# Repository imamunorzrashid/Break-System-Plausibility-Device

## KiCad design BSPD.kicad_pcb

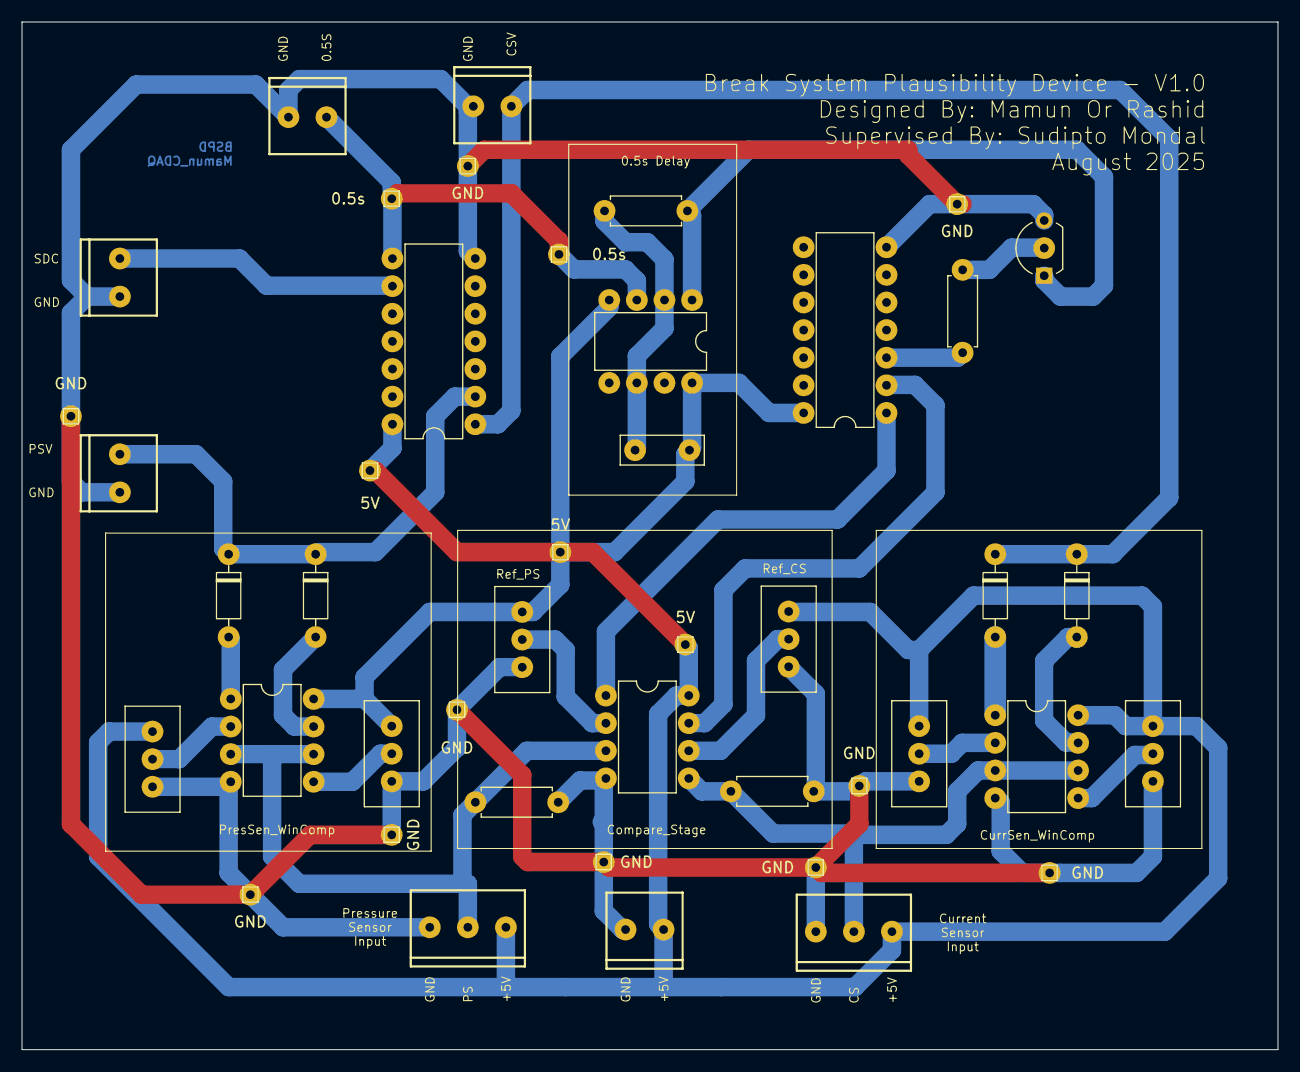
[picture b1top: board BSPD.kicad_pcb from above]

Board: 2 copper layers, 115.5 x 94.5 mm, 44 parts (0 on the bottom side), 24 nets.

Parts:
0.5s, 0.5s#2, 5V, 5V#2, 5V#3: TestPoint_THTPad_1.0x1.0mm_Drill0.5mm
C3: 10uF; C_Disc_D7.5mm_W2.5mm_P5.00mm
D1, D2, D3, D4: D; D_DO-35_SOD27_P7.62mm_Horizontal
GND: TestPoint_THTPad_1.0x1.0mm_Drill0.5mm
GND#2, GND#3, GND#4, GND#5, GND#6, GND#7, GND#8, GND#9, GND#10: TestPoint_THTPad_1.0x1.0mm_Drill0.5mm
J1, J2, J5, J6, J7: Screw_Terminal_3.5mm_2; Screw_Terminal_3.5mm-2
J3, J4: Screw_Terminal_3.5mm_3; Screw_Terminal_3.5mm-3
Q3: NPN; TO-92L_Inline_Wide
R1, R2, R21: 1k; R_Axial_DIN0207_L6.3mm_D2.5mm_P7.62mm_Horizontal
R4: 45.5k; R_Axial_DIN0207_L6.3mm_D2.5mm_P7.62mm_Horizontal
RV1, RV2: 10k; Potentiometer_Bourns_3296W_Vertical
RV3, RV4, RV5, RV6: 1k; Potentiometer_Bourns_3296W_Vertical
U1, U2, U6: LM358; DIP-8_W7.62mm
U3: 4075; DIP-14_W7.62mm
U4: LM555xN; DIP-8_W7.62mm
U7: SN74LS08N; DIP-14_W7.62mm

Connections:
+5V: 5V.1, 5V#2.1, 5V#3.1, C3.2, J3.3, J4.3, J7.2, RV1.1, RV2.1, RV3.1, RV4.1, RV5.1, RV6.1, U1.8 (V+), U2.8 (V+), U3.14 (VDD), U4.4 (R), U4.8 (VCC), U6.8 (V+), U7.14 (VCC)
/0.5s_delay: 0.5s.1, 0.5s#2.1, J5.1, U3.8, U4.3 (Q)
/2: C3.1, R4.2, U4.2 (TR), U4.6 (THR)
/Current_Comp_Out: U6.7, U7.2 (1B)
/Current_Sensor: J3.2, R2.1, U1.3 (+), U1.6 (-), U6.5 (+)
/Current_Sensor_Validated: D1.1 (K), D2.1 (K), J6.1, U3.1
/Pressure_Comp_Out: U6.1, U7.1 (1A)
/Pressure_Sensor: J4.2, R1.1, U2.3 (+), U2.6 (-), U6.3 (+)
/Pressure_Sensor_Validated: D3.1 (K), D4.1 (K), J2.1, U3.2
/SDC: J1.1, U3.9
GND: GND.1, GND#2.1, GND#3.1, GND#4.1, GND#5.1, GND#6.1, GND#7.1, GND#8.1, GND#9.1, GND#10.1, J1.2, J2.2, J3.1, J4.1, J5.2, J6.2, J7.1, Q3.3 (E), R1.2, R2.2, RV1.3, RV2.3, RV3.3, RV4.3, RV5.3, RV6.3, U1.4 (V-), U2.4 (V-), U3.7 (VSS), U6.4 (V-), U7.7 (GND)
unnamed: D1.2 (A), U1.1
unnamed: D2.2 (A), U1.7
unnamed: D3.2 (A), U2.1
unnamed: D4.2 (A), U2.7
unnamed: Q3.2 (B), R21.2
unnamed: Q3.1 (C), R4.1, U4.1 (GND)
unnamed: RV3.2, U1.2 (-)
unnamed: RV4.2, U1.5 (+)
unnamed: RV6.2, U2.2 (-)
unnamed: RV5.2, U2.5 (+)
unnamed: RV1.2, U6.2 (-)
unnamed: RV2.2, U6.6 (-)
unnamed: R21.1, U7.3 (1Y)

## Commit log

2025-07-31 commited - 01 August 2025
2025-07-31 Text Added
2025-07-31 Rounded PCB
2025-07-31 Dont know why
2025-07-31 Final Commit for print
2025-07-31 Solid Zone Added
2025-08-25 updated pcb with better clearance
2026-06-28 Add README for Brake System Plausibility Device
    Add detailed documentation for the Brake System Plausibility Device (BSPD), including features, system overview, circuit operation, hardware components, compliance, and future improvements.
2026-06-28 Create README.md for BSPD project
    Add detailed documentation for the Brake System Plausibility Device (BSPD), including features, system overview, circuit operation, hardware components, compliance, future improvements, and author in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
